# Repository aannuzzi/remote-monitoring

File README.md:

# remote-monitoring
Cal Poly Senior Project

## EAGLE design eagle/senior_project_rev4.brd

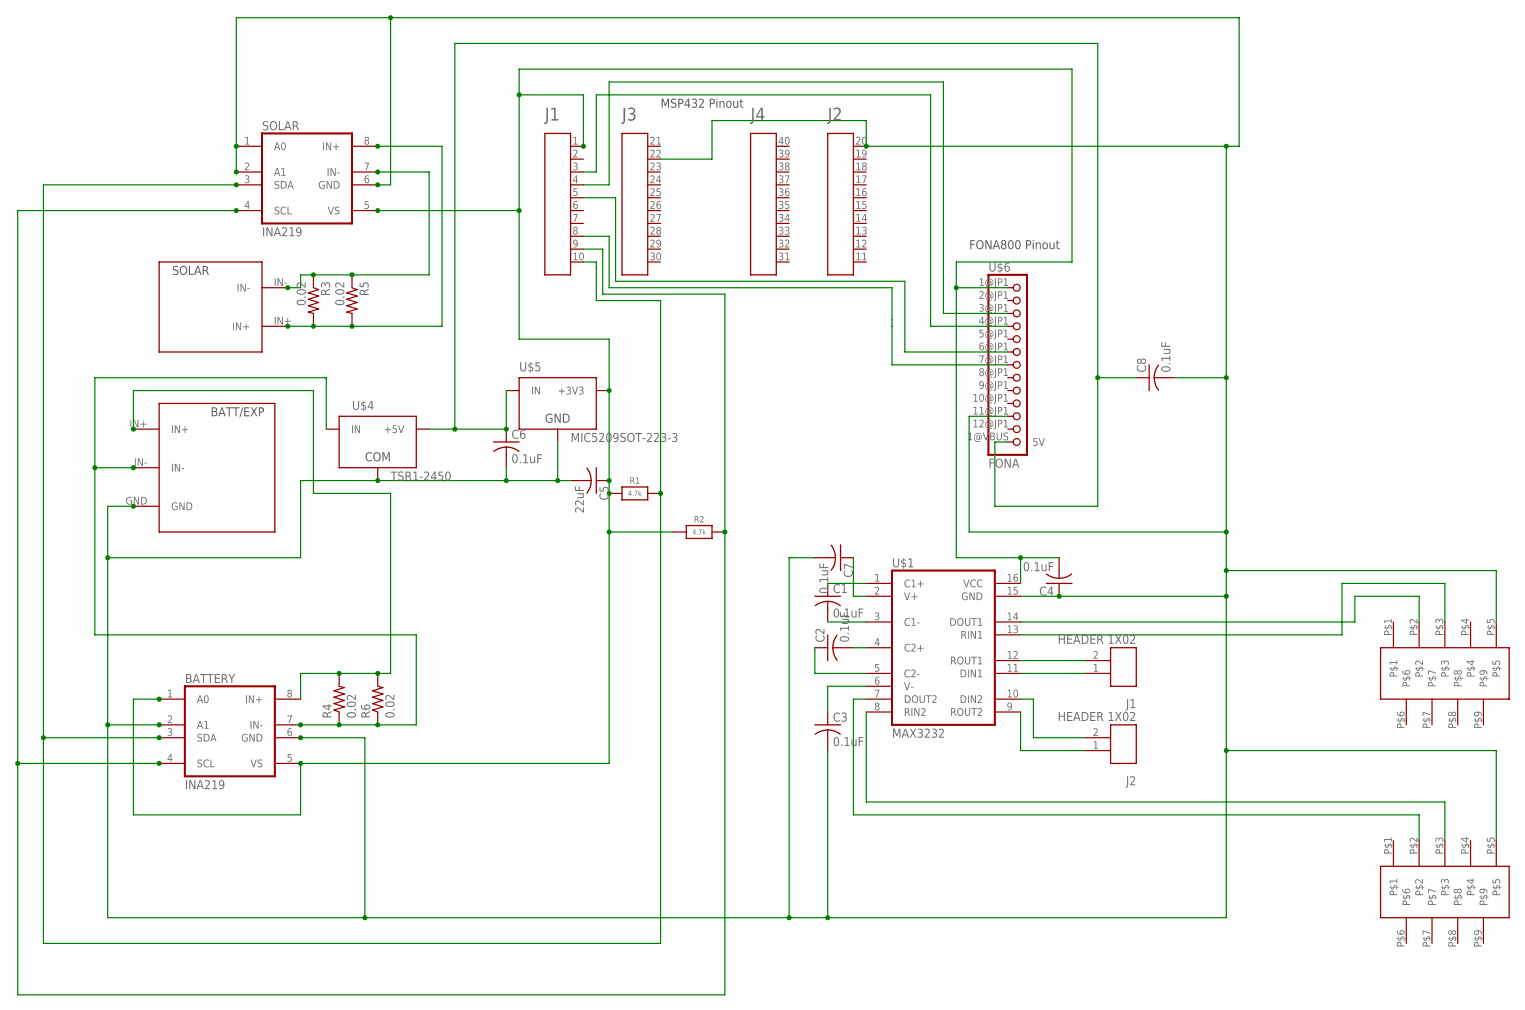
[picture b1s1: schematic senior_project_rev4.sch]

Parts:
A1: MSP432; 4X10-BOOSTERPACK
BATTERY: INA219; SO08
C1, C2, C3, C4, C6, C7, C8: 0.1uF; C1206
C5: 22uF; C1206
J1, J2: HEADER 1X02; 1X02
R1, R2: 4.7k; _1206
R3, R4, R5, R6: 0.02; R2512
RS232-1, RS232-2: XM2C-9; XM2C
SOLAR: INA219; SO08
U$1: MAX3232; SO16
U$2: TERM-3
U$3: TERM-2
U$4: TSR1-2450; TSR-1
U$5: MIC5209SOT-223-3; SOT-223
U$6: FONA; JP1_ADAFRUIT-FONA-800-GSM-BREAKOUT

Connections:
3.3V: A1.1, BATTERY.1 (A0), BATTERY.5 (VS), C4.2, C5.1, R1.1, R2.1, SOLAR.5 (VS), U$1.16 (VCC), U$5.3 (+3V3), U$6.1@JP1 (VIO)
5V: C6.1, C8.1, U$4.3 (+5V), U$5.1 (IN), U$6.1@VBUS (5V)
12V: BATTERY.7 (IN-), R4.1, R6.1, U$2.IN-, U$4.1 (IN)
GND: A1.20, A1.22, BATTERY.2 (A1), BATTERY.6 (GND), C3.2, C4.1, C5.2, C6.2, C7.2, C8.2, RS232-1.P$5, RS232-2.P$5, SOLAR.1 (A0), SOLAR.2 (A1), SOLAR.6 (GND), U$1.15 (GND), U$2.GND, U$4.2 (COM), U$5.2 (GND), U$5.4 (GND), U$6.11@JP1 (GND)
unnamed: C3.1, U$1.6 (V-)
unnamed: RS232-2.P$2, U$1.7 (DOUT2)
unnamed: A1.8, U$6.7@JP1 (PS)
unnamed: R3.1, R5.1, SOLAR.7 (IN-), U$3.IN-
unnamed: R3.2, R5.2, SOLAR.8 (IN+), U$3.IN+
unnamed: J1.2, U$1.12 (ROUT1)
unnamed: A1.10, BATTERY.3 (SDA), R1.2, SOLAR.3 (SDA)
unnamed: C1.2, U$1.3 (C1-)
unnamed: C1.1, U$1.1 (C1+)
unnamed: C2.2, U$1.4 (C2+)
unnamed: C2.1, U$1.5 (C2-)
unnamed: C7.1, U$1.2 (V+)
unnamed: RS232-1.P$2, U$1.14 (DOUT1)
unnamed: RS232-1.P$3, U$1.13 (RIN1)
unnamed: RS232-2.P$3, U$1.8 (RIN2)
unnamed: A1.9, BATTERY.4 (SCL), R2.2, SOLAR.4 (SCL)
unnamed: A1.5, U$6.6@JP1 (KEY)
unnamed: A1.4, U$6.3@JP1 (RX)
unnamed: A1.3, U$6.4@JP1 (TX)
unnamed: J1.1, U$1.11 (DIN1)
unnamed: J2.2, U$1.10 (DIN2)
unnamed: J2.1, U$1.9 (ROUT2)
unnamed: BATTERY.8 (IN+), R4.2, R6.2, U$2.IN+

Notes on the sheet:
MSP432 Pinout
FONA800 Pinout
SOLAR
BATT/EXP

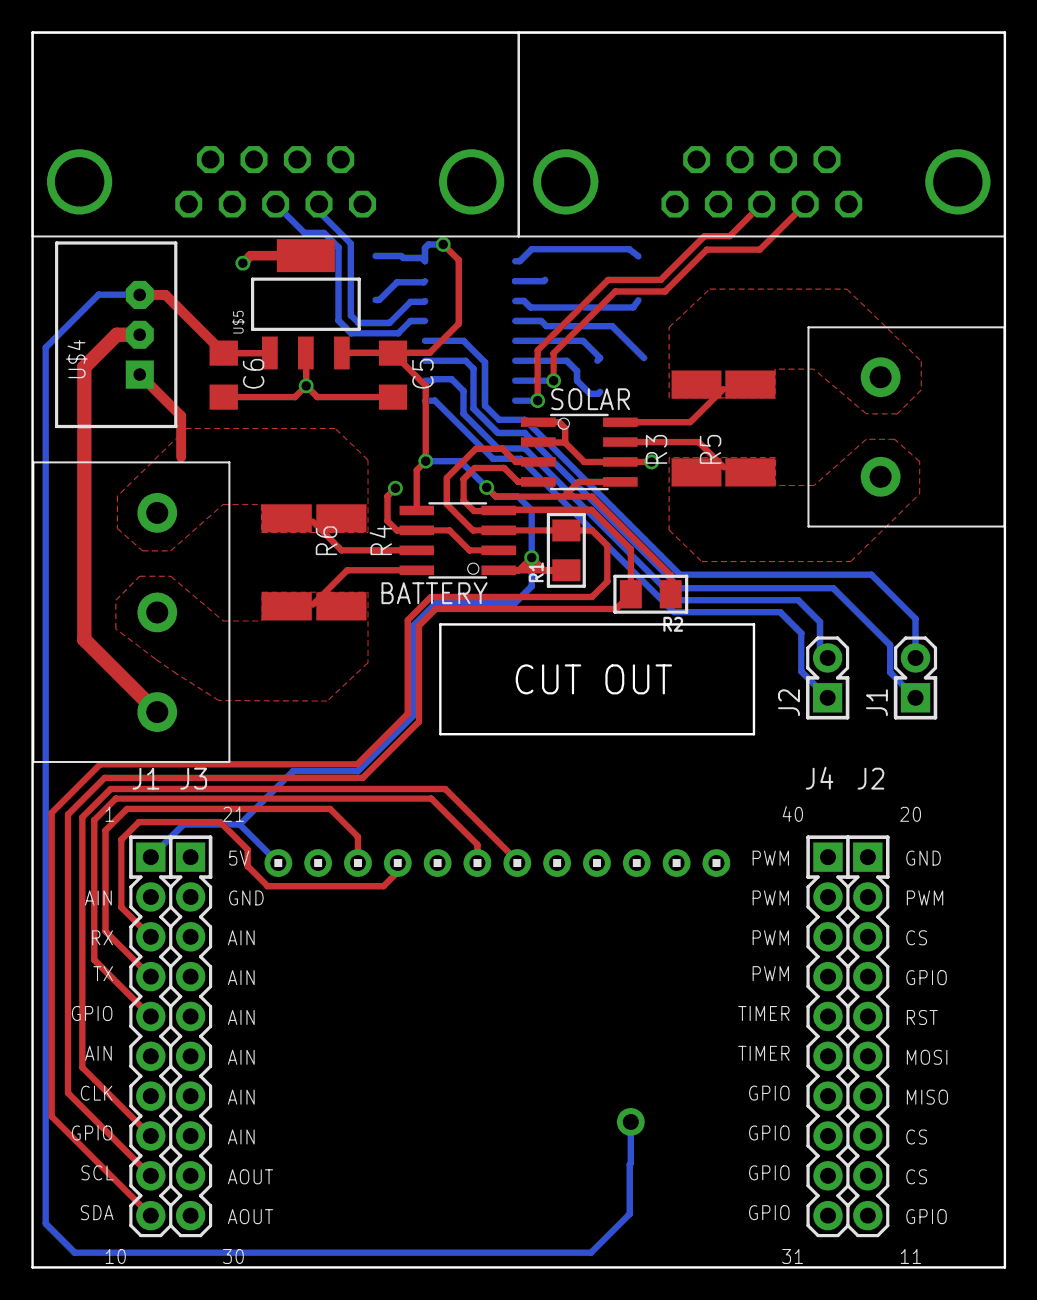
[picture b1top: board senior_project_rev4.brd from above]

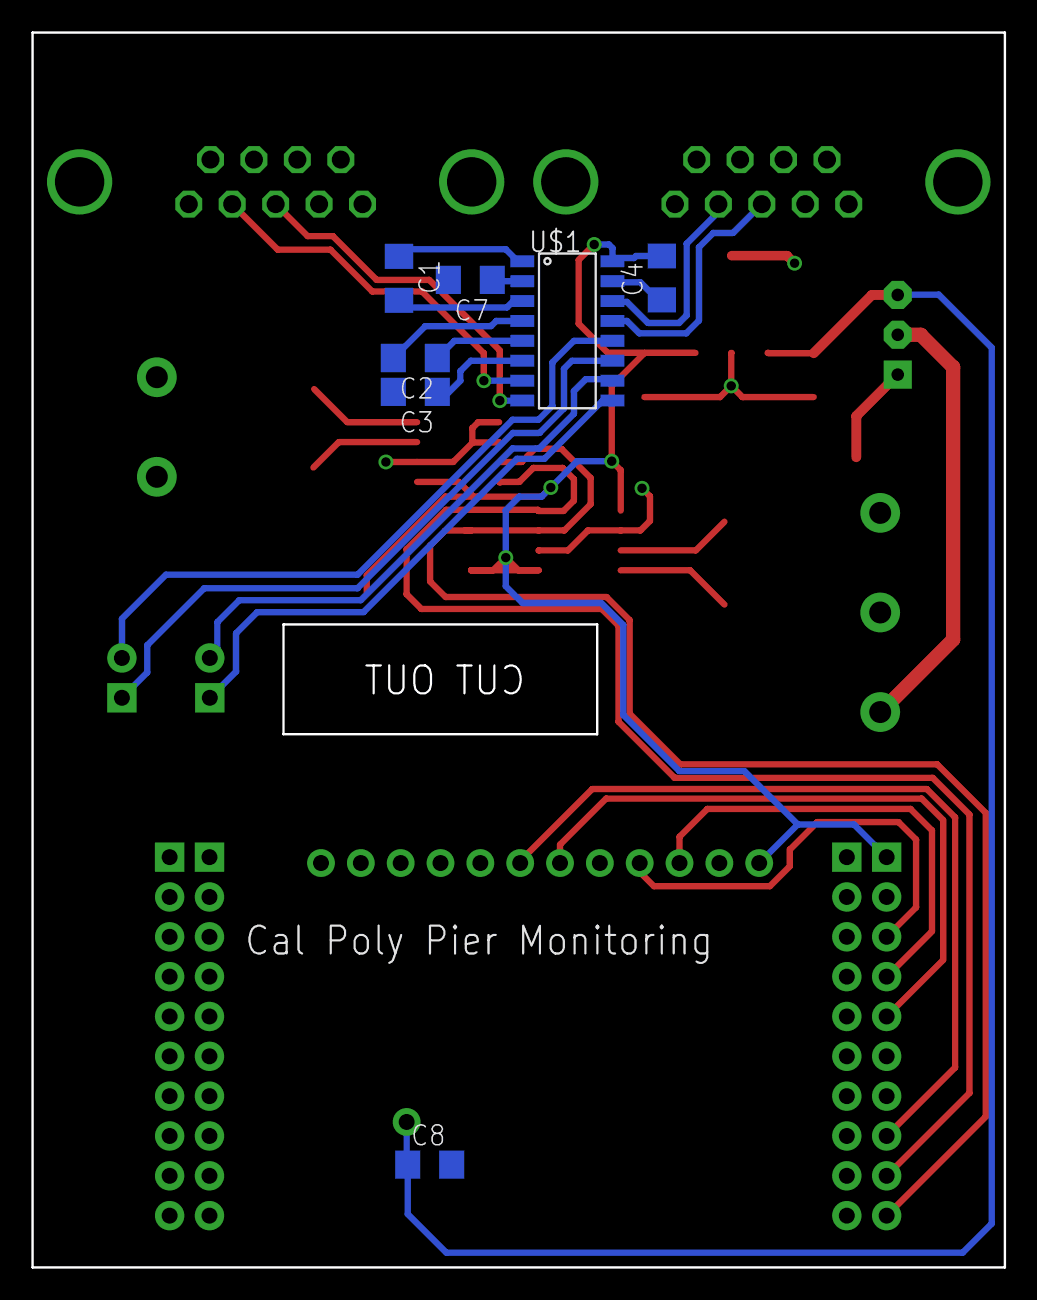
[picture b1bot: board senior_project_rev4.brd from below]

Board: 2 copper layers, 62.0 x 78.7 mm, 27 parts (7 on the bottom side), 27 nets.

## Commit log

2016-09-23 senior project
2016-09-23 project reports
